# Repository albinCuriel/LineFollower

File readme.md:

# LineFollower

Syntheseproject HOGENT Elektromechanica: een snelle linefollower (doel ≥ 1 m/s) met een ESP32-S3. De robot is gebouwd op een gaatjesprint die tegelijk het chassis is (plan B). De eigen print (plan A) wordt enkel ontworpen.

## specifications

| | |
|---|---|
| microcontroller | ESP32-S3 devkit N16R8 (dual USB-C), backup ATmega32U4 ([waarom](ontwerpkeuzes/onderdelenkeuze.md)) |
| motors | 2× GA12-N20 6V 10:1 (±1500 rpm) met Hall-encoder 7 PPR |
| h-bridge | TB6612FNG (1 module voor beide motoren) |
| sensors | Pololu QTR-8A (8 analoge reflectiesensoren, LEDON) |
| batteries | LiPo 2S 450 mAh 100C (XT30), 3,3 V via een CN3903-buck |
| wireless communication | wifi: eigen netwerk + TCP-terminal (gsm of laptop) |
| distance sensor - motors | 98,7 mm |
| weight | ±123 g (berekend uit de onderdelen, wordt gewogen na de bouw) |
| speed | simulatie op parcours 3: ±0,82 m/s gemiddeld met de veilige startwaarden; wordt gemeten op het parcours |
| afmetingen | 150 × 106 × 48 mm (L × B × H, met spoiler) |

## status (16/11/2026)

| Onderdeel | Status |
|---|---|
| ontwerp, BOM, schema, bekabelingsplan, 3D-model | klaar |
| proof of concepts (H-brug, sensor, interrupt, wifi) | klaar, compileren |
| basisprogramma + finale code | klaar, compileren (GitHub Action), 133 unit tests op de regelkern |
| simulatie + PID-afstelling | klaar (±0,82 m/s verwacht) |
| bouw op de gaatjesprint | bezig: stap 1–7 van de [instructable](instructable/readme.md) gesoldeerd, stap 8 (H-brug) bezig |
| plan A (eigen print) | ontworpen: schema, BOM met packages, gerouteerde print als chassis (DRC 0 fouten), gerbers en maattekening ([kicad_planA](technische%20tekeningen/elektronisch/kicad_planA/readme.md)); niet besteld |
| testritten, gemeten snelheid en gewicht | na de bouw |

## inhoud van deze repository

| Map | Inhoud |
|---|---|
| [bill of materials](bill%20of%20materials/readme.md) | onderdelenlijst met prijzen en bestelling |
| [ontwerpkeuzes](ontwerpkeuzes/readme.md) | waarom deze onderdelen, vergelijking van microcontrollers, snelheidsberekening |
| [technische tekeningen](technische%20tekeningen/readme.md) | elektrisch schema, bekabelingsplan, boormal, 3D-model, samenstellingstekening |
| [instructable](instructable/readme.md) | stappenplan om de robot te bouwen |
| [code](code/readme.md) | proof of concepts, basisprogramma en finale code |
| [simulatie](simulatie/readme.md) | de robot virtueel op parcours 3, met dezelfde regelcode: PID vooraf afgesteld |
| [gebruiksaanwijzing](gebruiksaanwijzing/readme.md) | opladen, verbinden, commando's, kalibreren |
| [datasheets](datasheets/readme.md) | datasheets van alle onderdelen |
| [parcours](parcours/readme.md) | testparcours |
| [images](images/readme.md) | foto's |

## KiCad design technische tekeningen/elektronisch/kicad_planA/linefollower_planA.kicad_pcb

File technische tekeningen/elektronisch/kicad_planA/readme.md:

# Plan A: eigen print (KiCad 10)

Volledige linefollower op één print van **100 × 130 mm** met losse SMD-onderdelen, zonder breakoutmodules. De print is tegelijk het chassis: motoren, ball caster en spoiler worden er rechtstreeks op geschroefd. Zelfde pinverdeling als plan B ([board.h](../../../code/board.h)), dus dezelfde firmware.

Plan A is ontworpen, niet besteld of gesoldeerd.

| Bovenkant | Onderkant (sensoren) |
|---|---|
|  |  |

## Bestanden

| Bestand | Inhoud |
|---|---|
| `linefollower_planA.kicad_pro` | het project: open dit in KiCad |
| `linefollower_planA.kicad_sch` | schema (ERC: 0 fouten) → [pdf](../elektrisch_schema_planA.pdf) |
| `linefollower_planA.kicad_pcb` | print, 2 lagen, volledig gerouteerd → [pdf boven](../pcb_planA.pdf), [pdf onder](../pcb_planA_onderkant.pdf) |
| [gerbers_planA.zip](gerbers_planA.zip) | productiebestanden (gerbers + boorbestand) voor JLCPCB/PCBWay |
| [drc_rapport.txt](drc_rapport.txt) | ontwerpcontrole: 0 fouten, 0 open verbindingen |
| [bom_planA.csv](bom_planA.csv) | onderdelenlijst met package per onderdeel (uit het schema); met prijzen in de [BOM](../../../bill%20of%20materials/readme.md) |
| [tekening_planA.pdf](../../mechanisch/tekening_planA.pdf) | mechanische maattekening: omtrek, uitsparingen, boorgaten |
| `planA_maten.py` | alle maten van de print (omtrek, uitsparingen, boorgaten) |
| `bouw_pcb.py` | bouwt de print uit de netlijst: plaatsing van elk onderdeel, omtrek, gaten, GND-vlakken |
| `route_pcb.py` | netklassen + routeren met Freerouting |
| `maattekening.py` | maakt de maattekening |

## Blokken

| Blok | Onderdelen | Opmerking |
|---|---|---|
| Voeding | J1 XT30, **Q10 AO3401A** + R8 + SW1, U2 **AP63203WU** (3,3 V, 2 A) + L1 6,8 µH, C1–C4 | aan/uit: de schuifschakelaar SW1 stuurt enkel de gate van de P-MOSFET Q10. De batterijstroom loopt door de MOSFET (4 A), niet door de kleine schakelaar (0,3 A) |
| USB | J4 USB-C, R20/R21 5,1 kΩ (CC), D1 **B5819W** | USB voedt via D1 de VBAT-lijn. De diode spert zodra de batterij aan staat (8,4 V > 5 V): **USB en batterij tegelijk is hier veilig** |
| Microcontroller | U1 **ESP32-S3-WROOM-1-N16R8**, C6/C7, RESET (SW4 + R4/C8), BOOT (SW3 + R5), J5 UART | antenne over de linkerrand, geen koper eronder. Kristal en flash zitten in de module. Programmeren via de ingebouwde USB (GPIO19/20), geen ISP-pinnen nodig; UART op J5 als reserve |
| Sensoren | Q1–Q8 **QRE1113GR** (onderkant), R10–R17 100 Ω (IR-led), R22–R29 47 kΩ (pull-up), Q9 **AO3400A** (LEDON) | zelfde schakeling als de QTR-8A; GPIO1–8 (ADC1), LEDON = GPIO11 |
| Motorsturing | U3 **TB6612FNG** (SSOP-24), C10–C12, J2/J3 JST-ZH 6-pins | hardware-PWM op GPIO12/15, richting 13/14 en 16/17, STBY 18, encoders 39–42. VM = batterij, VCC = 3,3 V |
| Bediening | SW2 start/stop (GPIO21, interrupt), D2 power-led, D3 **WS2812B** statusled (GPIO48) | |
| Batterijmeting | R1 10 kΩ / R2 5,1 kΩ + C5 100 nF | GPIO9 |

## Checklist uit de cursus

### Schema
| Punt | Hoe opgelost |
|---|---|
| aansluiting batterij | J1 XT30 (haaks, op de achterrand) |
| voltage regulator + afvlak- en ontstoorcondensatoren | U2 AP63203 met C1 (ingang 10 µF), C2 (bootstrap), L1, C3/C4 (uitgang 2 × 22 µF) |
| indicator-led | D2 + R3 op 3,3 V (power), D3 RGB (status) |
| µC: ontstoorcondensatoren | C6 10 µF + C7 100 nF vlak naast de 3V3-pin |
| µC: kristal | in de module ingebouwd |
| usb-connector | J4 met CC-weerstanden; D+/D− rechtstreeks naar GPIO20/19 |
| start/stop-knop (interrupt) | SW2 op GPIO21 |
| resetknop | SW4 op EN met R4/C8 (RC-vertraging) |
| isp-pinnen | niet nodig: de ESP32-S3 programmeert via USB; BOOT-knop SW3 + UART J5 als noodoplossing |
| ongebruikte pinnen | met een no-connect-vlag in het schema; GPIO35–37 blijven vrij (bezet door het PSRAM van de N16R8) |
| communicatie | wifi zit in de module: geen rx/tx-kruising, geen level shifter |
| H-brug: logische en vermogenspanning | VCC = 3,3 V, VM = VBAT met C10 10 µF + C11 100 nF |
| H-brug: PWM- en richtingspinnen, connectoren | zie blokken; J2/J3 dragen motor én encoder |
| sensoren: weerstanden | 100 Ω per IR-led (±20 mA op 3,3 V), 47 kΩ pull-up per fototransistor |
| bevestigingsgaten | 4 × motorbeugel, 2 × caster, 2 × spoiler ([maattekening](../../mechanisch/tekening_planA.pdf)) |
| BOM aangepast naar plan A, leverancier en package per onderdeel | [BOM plan A](../../../bill%20of%20materials/readme.md) |
| ERC uitgevoerd | 0 fouten. De resterende waarschuwingen zeggen enkel dat de standaardbibliotheken van KiCad niet in de projectmap staan |

### Print
| Punt | Hoe opgelost |
|---|---|
| korte, dikke banen tussen voeding, H-brug en motoren | XT30, Q10, U2 en U3 liggen achteraan bij elkaar, tussen de motoren |
| regulator en condensatoren tegen elkaar | C1, C2, L1, C3, C4 rond U2 |
| µC en ontstoorcondensatoren tegen elkaar | C6/C7 naast U1 |
| usb-connector op de rand, kabel van de print weg | J4 op de achterrand |
| denk 3-dimensionaal | motoren, caster en sensoren aan de onderkant; hoge onderdelen (XT30, USB, stekkers) buiten de motorzone |
| sensoren vooraan, onderkant, loodrecht op de rijrichting | Q1–Q8 op 5 mm van de voorrand, 99 mm voor de wielas |
| motoren achteraan, gewichtsverdeling | wielas op 26 mm van de achterrand, batterij erboven |
| niet breder dan nodig | wielen in uitsparingen: de robot is 100 mm breed (chronobrug 120 mm) |
| analoog en digitaal gescheiden | sensoren vooraan, vermogen (motoren, buck) achteraan |
| groundplane | GND-vlak op beide lagen, met volle padverbinding; uitsparing onder de antenne |
| DRC uitgevoerd | 0 fouten, 0 open verbindingen. 3 waarschuwingen: de opdruk van de XT30 steekt over de achterrand (de stekker steekt bewust uit) |

### Spoorbreedtes

| Netklasse | Netten | Breedte | Stroom |
|---|---|---|---|
| Batterij | BATT+ | 1,0 mm | tot ±1,5 A |
| Vermogen | VBAT, motoren, schakelknoop buck | 0,6 mm | motor: 0,55 A bij blokkeren |
| Voeding | +3V3 | 0,5 mm | ±0,5 A piek (wifi) |
| USB | D+, D−, CC, VBUS | 0,25 mm | pads van 0,3 mm op 0,5 mm steek |
| Signaal | de rest | 0,3 mm | breedte van de IC-pinnen |
| GND | | vlak op 2 lagen | |

De vuistregel uit de cursus (vermogen 2,54 mm, voeding 1,27 mm) past niet op de pinnen van de TB6612 (0,65 mm steek), de AP63203 en de USB-C-connector. De cursus laat daarom ook "de breedte van de pinnen" toe. Controle met IPC-2221 (35 µm koper, buitenlaag, 10 °C opwarming): 0,6 mm draagt 1,6 A en 1,0 mm draagt 2,4 A. De grootste stromen zijn 0,55 A per motor en ±1,5 A totaal, dus er is een marge van minstens factor 1,6. De retourstroom loopt door het GND-vlak.

## Opnieuw opbouwen
```
kicad-cli sch export netlist --format kicadxml -o planA_netlijst.xml linefollower_planA.kicad_sch
"<KiCad>\bin\python.exe" bouw_pcb.py planA_netlijst.xml
"<KiCad>\bin\python.exe" route_pcb.py <pad naar freerouting-1.9.0.jar>      (2x draaien als er nog een verbinding open is)
kicad-cli pcb drc linefollower_planA.kicad_pcb
kicad-cli pcb export gerbers -o gerbers linefollower_planA.kicad_pcb
```

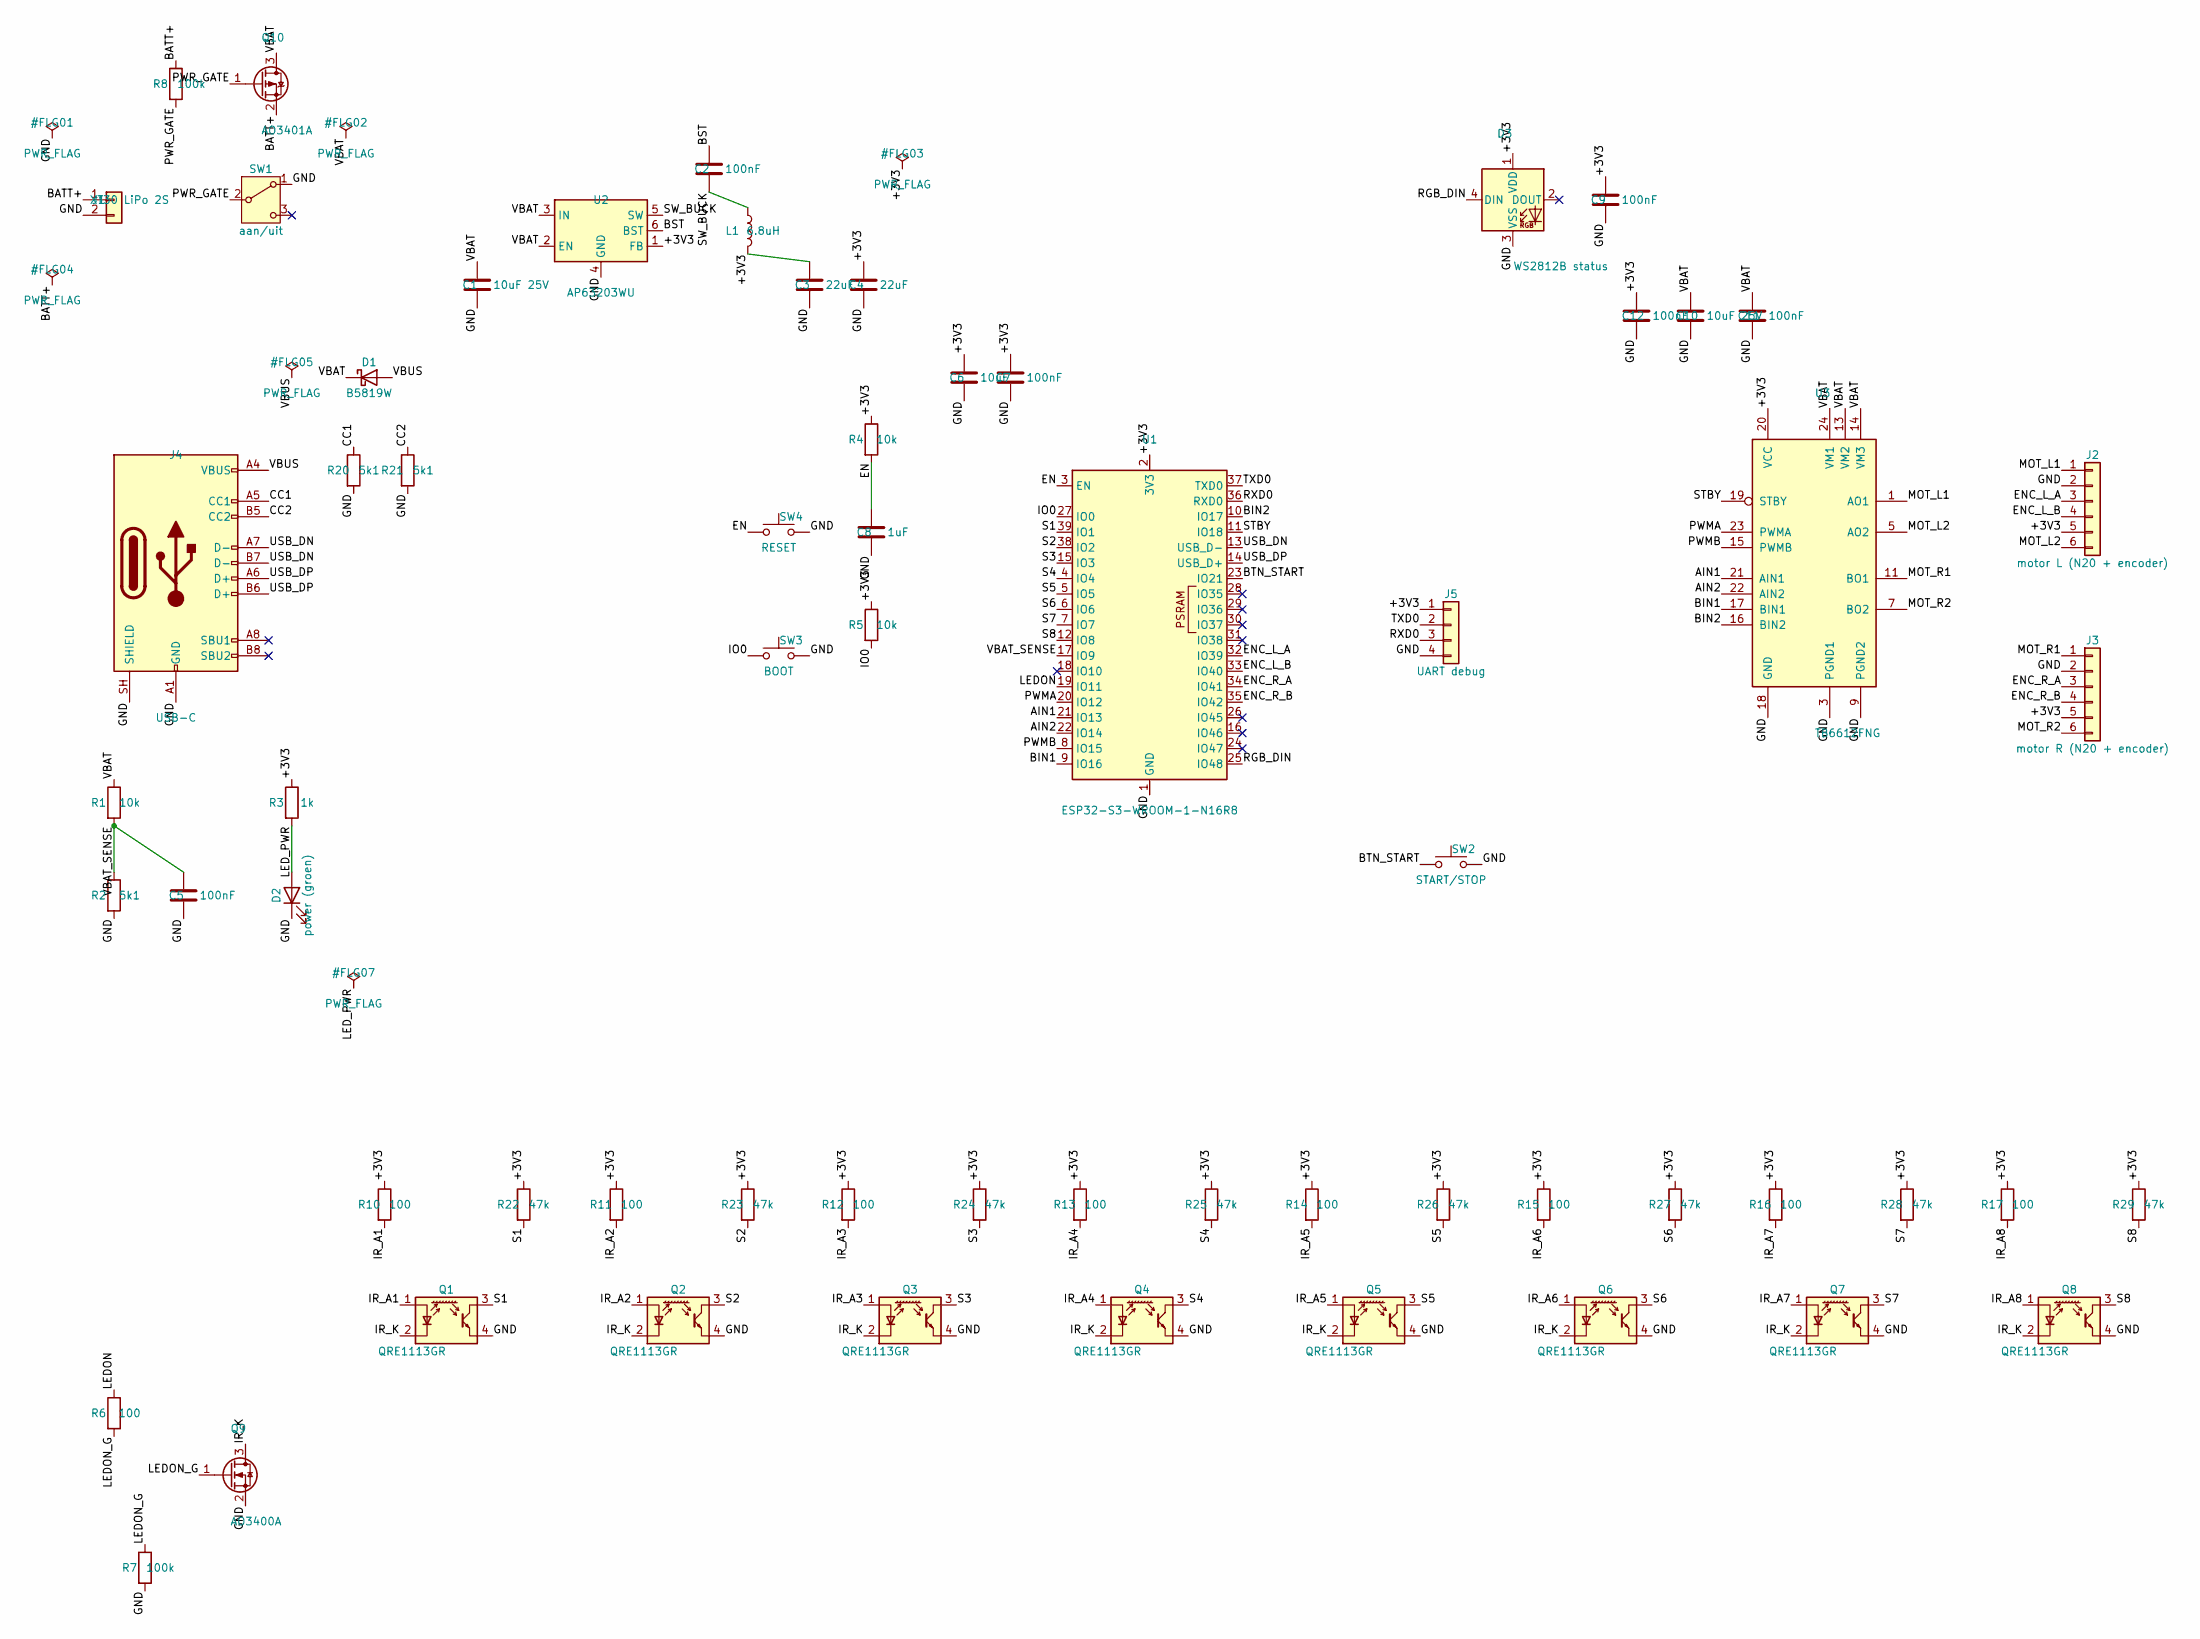
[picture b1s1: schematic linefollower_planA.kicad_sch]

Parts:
C1, C10: 10uF 25V; C_1206_3216Metric
C2, C5, C7, C9, C11, C12: 100nF; C_0805_2012Metric
C3, C4: 22uF; C_1206_3216Metric
C6: 10uF; C_0805_2012Metric
C8: 1uF; C_0805_2012Metric
D1: B5819W; D_SOD-123
D2: power (groen); LED_0805_2012Metric
D3: WS2812B status; LED_WS2812B_PLCC4_5.0x5.0mm_P3.2mm
J1: XT30 LiPo 2S; AMASS_XT30PW-M_1x02_P2.50mm_Horizontal
J2: motor L (N20 + encoder); JST_ZH_B6B-ZR_1x06_P1.50mm_Vertical
J3: motor R (N20 + encoder); JST_ZH_B6B-ZR_1x06_P1.50mm_Vertical
J4: USB-C; USB_C_Receptacle_GCT_USB4105-xx-A_16P_TopMnt_Horizontal
J5: UART debug; PinHeader_1x04_P2.54mm_Vertical
L1: 6.8uH; L_Bourns-SRN4018
Q1, Q2, Q3, Q4, Q5, Q6, Q7, Q8: QRE1113GR; OnSemi_CASE100CY
Q9: AO3400A; SOT-23
Q10: AO3401A; SOT-23
R1, R4, R5: 10k; R_0805_2012Metric
R2, R20, R21: 5k1; R_0805_2012Metric
R3: 1k; R_0805_2012Metric
R6: 100; R_0805_2012Metric
R7, R8: 100k; R_0805_2012Metric
R10, R11, R12, R13, R14, R15, R16, R17: 100; R_0603_1608Metric
R22, R23, R24, R25, R26, R27, R28, R29: 47k; R_0603_1608Metric
SW1: aan/uit; SW_SPDT_PCM12
SW2: START/STOP; SW_SPST_TL3342
SW3: BOOT; SW_SPST_TL3342
SW4: RESET; SW_SPST_TL3342
U1: ESP32-S3-WROOM-1-N16R8; ESP32-S3-WROOM-1
U2: AP63203WU; TSOT-23-6
U3: TB6612FNG; SSOP-24_5.3x8.2mm_P0.65mm

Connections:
+3V3: C3.1, C4.1, C6.1, C7.1, C9.1, C12.1, D3.1 (VDD), J2.5, J3.5, J5.1, L1.2, R3.1, R4.1, R5.1, R10.1, R11.1, R12.1, R13.1, R14.1, R15.1, R16.1, R17.1, R22.1, R23.1, R24.1, R25.1, R26.1, R27.1, R28.1, R29.1, U1.2 (3V3), U2.1 (FB), U3.20 (VCC)
AIN1: U1.21 (IO13), U3.21 (AIN1)
AIN2: U1.22 (IO14), U3.22 (AIN2)
BATT+: J1.1, Q10.2 (S), R8.1
BIN1: U1.9 (IO16), U3.17 (BIN1)
BIN2: U1.10 (IO17), U3.16 (BIN2)
BST: C2.1, U2.6 (BST)
BTN_START: SW2.1, U1.23 (IO21)
CC1: J4.A5 (CC1), R20.1
CC2: J4.B5 (CC2), R21.1
EN: C8.1, R4.2, SW4.1, U1.3 (EN)
ENC_L_A: J2.3, U1.32 (IO39)
ENC_L_B: J2.4, U1.33 (IO40)
ENC_R_A: J3.3, U1.34 (IO41)
ENC_R_B: J3.4, U1.35 (IO42)
GND: C1.2, C3.2, C4.2, C5.2, C6.2, C7.2, C8.2, C9.2, C10.2, C11.2, C12.2, D2.1 (K), D3.3 (VSS), J1.2, J2.2, J3.2, J4.A1 (GND), J4.A12 (GND), J4.B1 (GND), J4.B12 (GND), J4.SH (SHIELD), J5.4, Q1.4, Q2.4, Q3.4, Q4.4, Q5.4, Q6.4, Q7.4, Q8.4, Q9.2 (S), R2.2, R7.2, R20.2, R21.2, SW1.1 (A), SW2.2, SW3.2, SW4.2, U1.1 (GND), U1.40 (GND), U1.41 (GND), U2.4 (GND), U3.3 (PGND1), U3.4 (PGND1), U3.9 (PGND2), U3.10 (PGND2), U3.18 (GND)
IO0: R5.2, SW3.1, U1.27 (IO0)
IR_A1: Q1.1 (A), R10.2
IR_A2: Q2.1 (A), R11.2
IR_A3: Q3.1 (A), R12.2
IR_A4: Q4.1 (A), R13.2
IR_A5: Q5.1 (A), R14.2
IR_A6: Q6.1 (A), R15.2
IR_A7: Q7.1 (A), R16.2
IR_A8: Q8.1 (A), R17.2
IR_K: Q1.2 (K), Q2.2 (K), Q3.2 (K), Q4.2 (K), Q5.2 (K), Q6.2 (K), Q7.2 (K), Q8.2 (K), Q9.3 (D)
LEDON: R6.1, U1.19 (IO11)
LEDON_G: Q9.1 (G), R6.2, R7.1
LED_PWR: D2.2 (A), R3.2
MOT_L1: J2.1, U3.1 (AO1), U3.2 (AO1)
MOT_L2: J2.6, U3.5 (AO2), U3.6 (AO2)
MOT_R1: J3.1, U3.11 (BO1), U3.12 (BO1)
MOT_R2: J3.6, U3.7 (BO2), U3.8 (BO2)
PWMA: U1.20 (IO12), U3.23 (PWMA)
PWMB: U1.8 (IO15), U3.15 (PWMB)
PWR_GATE: Q10.1 (G), R8.2, SW1.2 (B)
RGB_DIN: D3.4 (DIN), U1.25 (IO48)
RXD0: J5.3, U1.36 (RXD0)
S1: Q1.3, R22.2, U1.39 (IO1)
S2: Q2.3, R23.2, U1.38 (IO2)
S3: Q3.3, R24.2, U1.15 (IO3)
S4: Q4.3, R25.2, U1.4 (IO4)
S5: Q5.3, R26.2, U1.5 (IO5)
S6: Q6.3, R27.2, U1.6 (IO6)
S7: Q7.3, R28.2, U1.7 (IO7)
S8: Q8.3, R29.2, U1.12 (IO8)
STBY: U1.11 (IO18), U3.19 (STBY)
SW_BUCK: C2.2, L1.1, U2.5 (SW)
TXD0: J5.2, U1.37 (TXD0)
USB_DN: J4.A7 (D-), J4.B7 (D-), U1.13 (USB_D-)
USB_DP: J4.A6 (D+), J4.B6 (D+), U1.14 (USB_D+)
VBAT: C1.1, C10.1, C11.1, D1.1 (K), Q10.3 (D), R1.1, U2.2 (EN), U2.3 (IN), U3.13 (VM2), U3.14 (VM3), U3.24 (VM1)
VBAT_SENSE: C5.1, R1.2, R2.1, U1.17 (IO9)
VBUS: D1.2 (A), J4.A4 (VBUS), J4.A9 (VBUS), J4.B4 (VBUS), J4.B9 (VBUS)

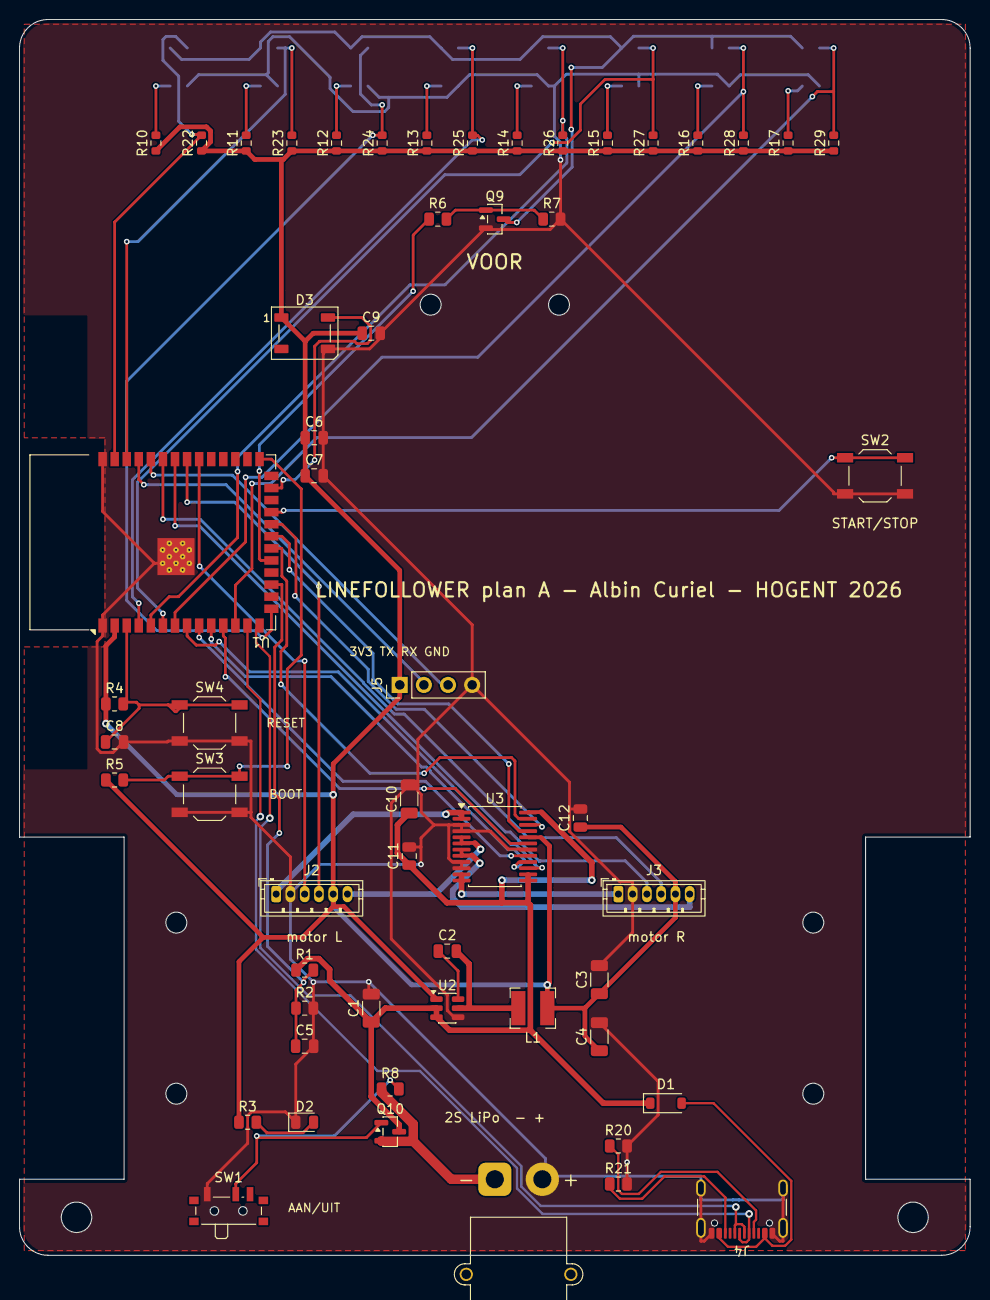
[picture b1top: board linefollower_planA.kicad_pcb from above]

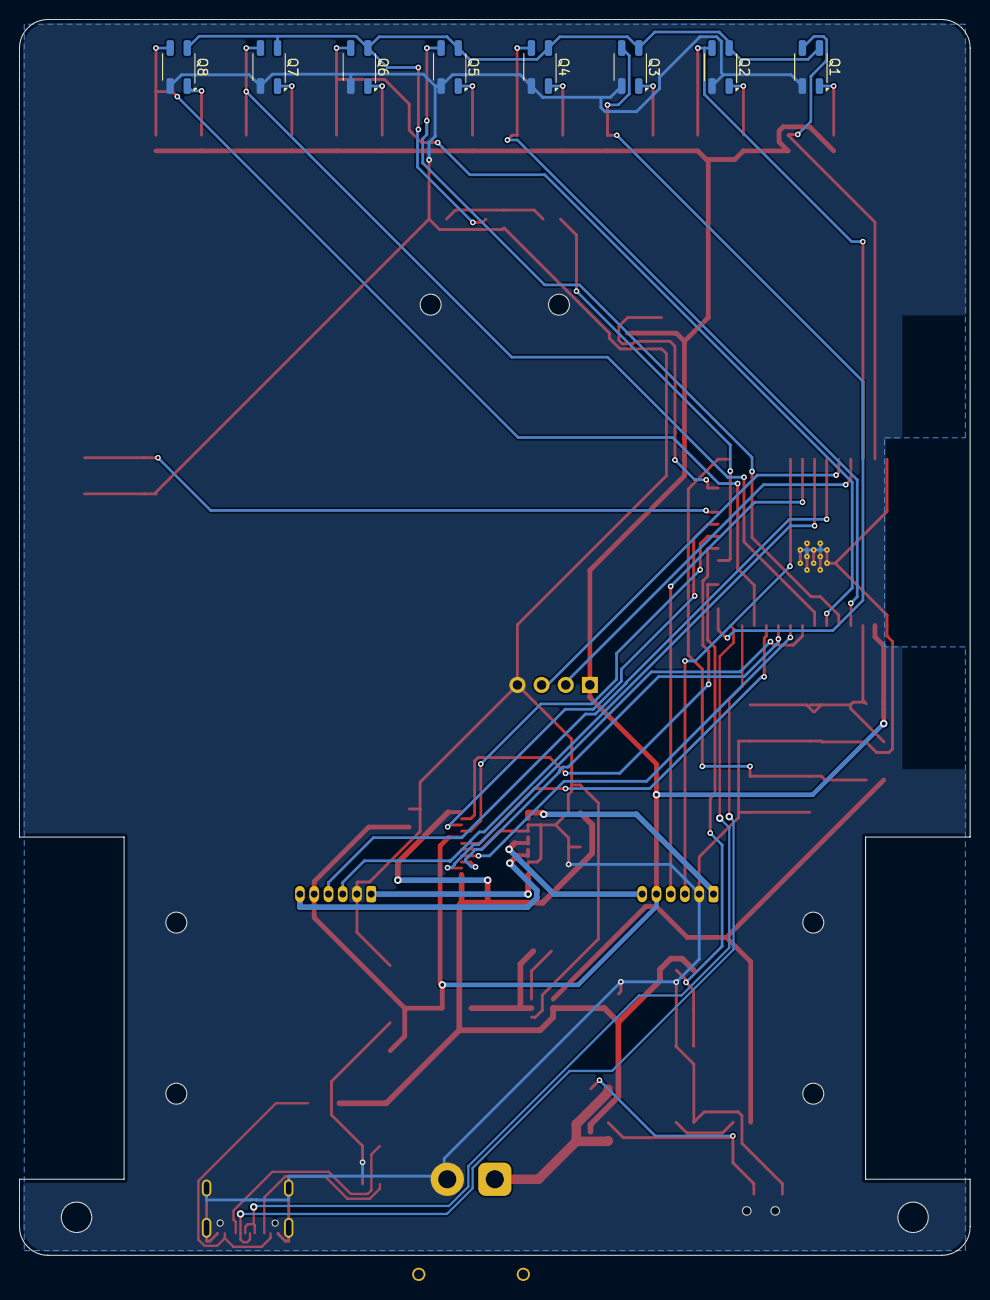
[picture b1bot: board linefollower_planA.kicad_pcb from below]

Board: 2 copper layers, 100.0 x 130.0 mm, 72 parts (8 on the bottom side), 54 nets.

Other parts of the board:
H1, H2: motorbeugel L; MountingHole_2.2mm_M2
H3, H4: motorbeugel R; MountingHole_2.2mm_M2
H5, H6: ball caster; MountingHole_2.2mm_M2
H7, H8: spoiler; MountingHole_3.2mm_M3

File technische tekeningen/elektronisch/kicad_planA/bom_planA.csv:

"Referenties","Waarde","Package (footprint)","Aantal"
"C1,C10","10uF 25V","Capacitor_SMD:C_1206_3216Metric","2"
"C2,C5,C7,C9,C11,C12","100nF","Capacitor_SMD:C_0805_2012Metric","6"
"C3,C4","22uF","Capacitor_SMD:C_1206_3216Metric","2"
"C6","10uF","Capacitor_SMD:C_0805_2012Metric","1"
"C8","1uF","Capacitor_SMD:C_0805_2012Metric","1"
"D1","B5819W","Diode_SMD:D_SOD-123","1"
"D2","power (groen)","LED_SMD:LED_0805_2012Metric","1"
"D3","WS2812B status","LED_SMD:LED_WS2812B_PLCC4_5.0x5.0mm_P3.2mm","1"
"J1","XT30 LiPo 2S","Connector_AMASS:AMASS_XT30PW-M_1x02_P2.50mm_Horizontal","1"
"J2","motor L (N20 + encoder)","Connector_JST:JST_ZH_B6B-ZR_1x06_P1.50mm_Vertical","1"
"J3","motor R (N20 + encoder)","Connector_JST:JST_ZH_B6B-ZR_1x06_P1.50mm_Vertical","1"
"J4","USB-C","Connector_USB:USB_C_Receptacle_GCT_USB4105-xx-A_16P_TopMnt_Horizontal","1"
"J5","UART debug","Connector_PinHeader_2.54mm:PinHeader_1x04_P2.54mm_Vertical","1"
"L1","6.8uH","Inductor_SMD:L_Bourns-SRN4018","1"
"Q1-Q8","QRE1113GR","OptoDevice:OnSemi_CASE100CY","8"
"Q9","AO3400A","Package_TO_SOT_SMD:SOT-23","1"
"Q10","AO3401A","Package_TO_SOT_SMD:SOT-23","1"
"R1,R4,R5","10k","Resistor_SMD:R_0805_2012Metric","3"
"R2,R20,R21","5k1","Resistor_SMD:R_0805_2012Metric","3"
"R3","1k","Resistor_SMD:R_0805_2012Metric","1"
"R6","100","Resistor_SMD:R_0805_2012Metric","1"
"R7,R8","100k","Resistor_SMD:R_0805_2012Metric","2"
"R10-R17","100","Resistor_SMD:R_0603_1608Metric","8"
"R22-R29","47k","Resistor_SMD:R_0603_1608Metric","8"
"SW1","aan/uit","Button_Switch_SMD:SW_SPDT_PCM12","1"
"SW2","START/STOP","Button_Switch_SMD:SW_SPST_TL3342","1"
"SW3","BOOT","Button_Switch_SMD:SW_SPST_TL3342","1"
"SW4","RESET","Button_Switch_SMD:SW_SPST_TL3342","1"
"U1","ESP32-S3-WROOM-1-N16R8","RF_Module:ESP32-S3-WROOM-1","1"
"U2","AP63203WU","Package_TO_SOT_SMD:TSOT-23-6","1"
"U3","TB6612FNG","Package_SO:SSOP-24_5.3x8.2mm_P0.65mm","1"

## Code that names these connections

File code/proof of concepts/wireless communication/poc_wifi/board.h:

// board.h - hardwarelaag linefollower (ESP32-S3 devkit N8R2, plan B gaatjesprint)
// Pinverdeling = KiCad-schema "technische tekeningen/elektronisch/kicad" + bedradingslijst.md.
// Wissel je ooit naar het backupbord (ATmega32U4), dan verandert enkel dit bestand.
#pragma once
#include <Arduino.h>

// --- QTR-8A sensorarray (ADC1, werkt ook met wifi aan) ---
static const uint8_t PIN_SENSOR[8] = {1, 2, 3, 4, 5, 6, 7, 8};
static const uint8_t PIN_LEDON     = 11;   // IR-leds van de QTR aan/uit

// --- Batterijmeting: deler 10k / 5,1k ---
static const uint8_t PIN_VBAT      = 9;
static const float   VBAT_DELER    = (10.0f + 5.1f) / 5.1f;    // 8,4 V -> 2,84 V

// --- TB6612FNG ---
static const uint8_t PIN_PWMA = 12, PIN_AIN1 = 13, PIN_AIN2 = 14;   // motor links
static const uint8_t PIN_PWMB = 15, PIN_BIN1 = 16, PIN_BIN2 = 17;   // motor rechts
static const uint8_t PIN_STBY = 18;                                 // laag = motoren uit
static const uint32_t PWM_FREQ = 20000;  // 20 kHz: niet hoorbaar
static const uint8_t  PWM_BITS = 10;     // 0..1023
static const int      PWM_MAX  = (1 << PWM_BITS) - 1;

// --- Encoders (Hall, 7 PPR op de motoras) ---
static const uint8_t PIN_ENC_L_A = 39, PIN_ENC_L_B = 40;
static const uint8_t PIN_ENC_R_A = 41, PIN_ENC_R_B = 42;

// --- Bediening en weergave ---
static const uint8_t PIN_BTN = 21;   // start/stop naar GND, interne pull-up
static const uint8_t PIN_RGB = 48;   // ingebouwde RGB-led van de devkit (= RGB_BUILTIN; op sommige klonen 38)
